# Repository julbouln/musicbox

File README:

Deprecated, see https://github.com/julbouln/musicboxV2

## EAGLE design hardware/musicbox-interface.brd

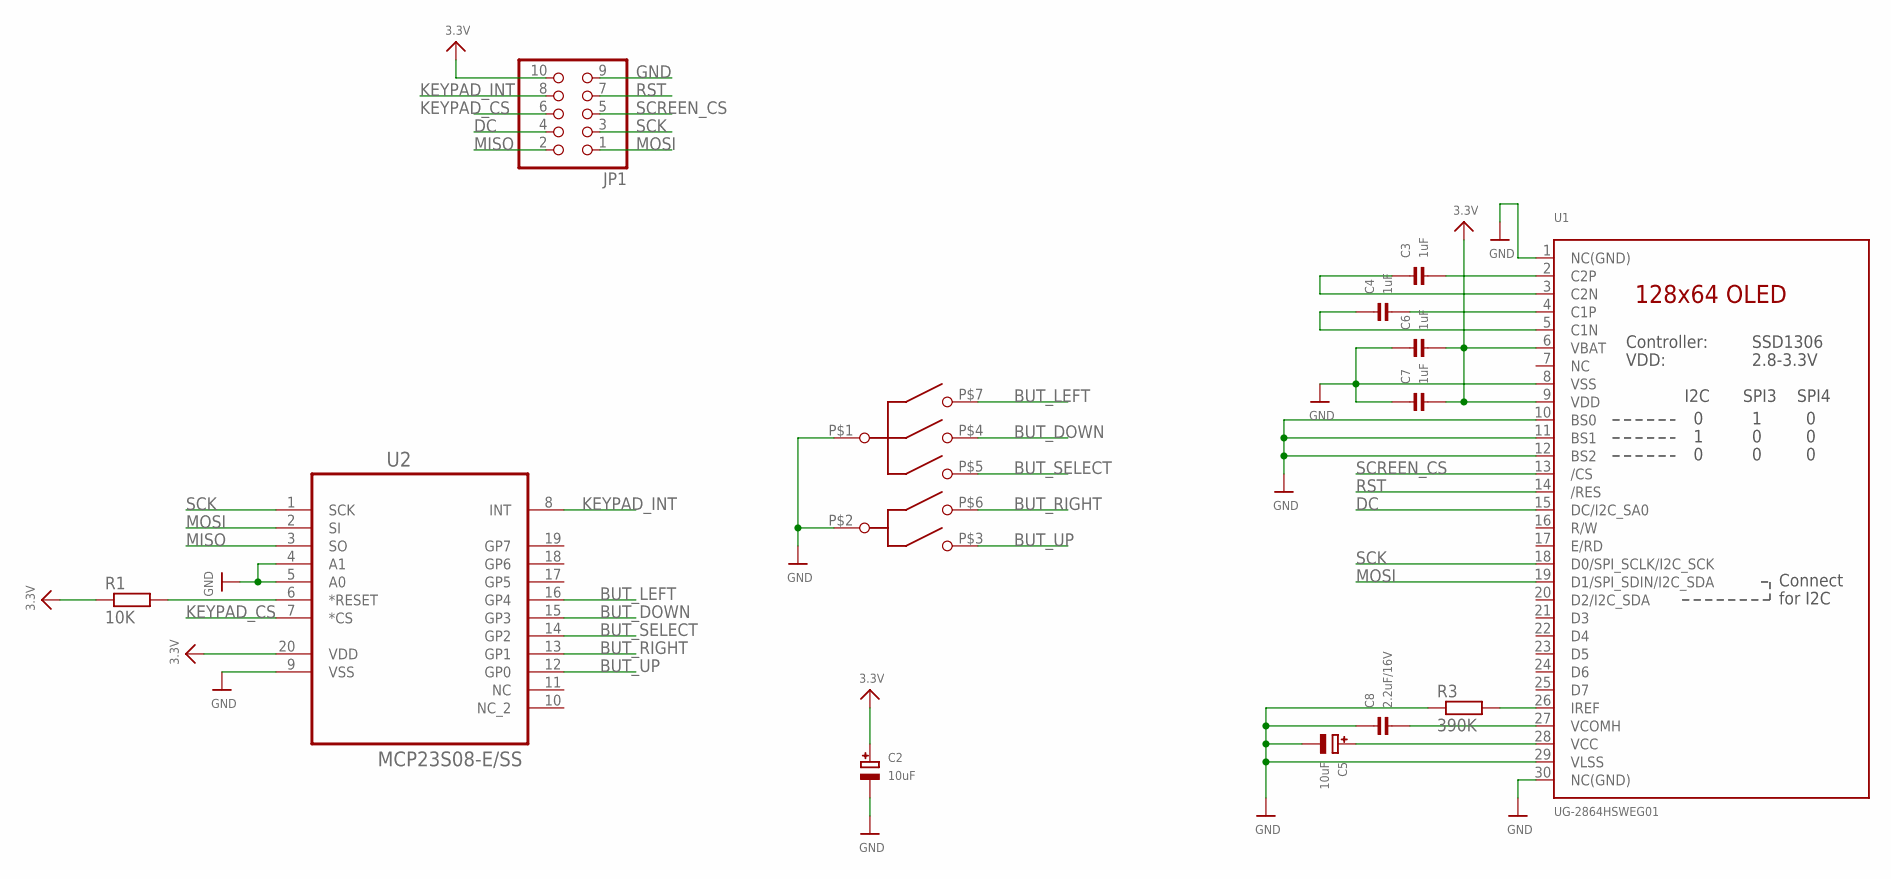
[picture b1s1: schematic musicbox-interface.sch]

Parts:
C2, C5: 10uF; EIA3216-18/A-R
C3, C4, C6, C7: 1uF; 0603
C8: 2.2uF/16V; 0603
JP1: HEADER-2X5; 2X05
R1: 10K; R0603
R3: 390K; R0603
U1: UG-2864HSWEG01; UG-2864HSWEG01_0.96IN_WRAPAROUND
U2: MCP23S08-E/SS; SOP65P780X200-20N
U$5: TPA; SMT

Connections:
3.3V: C2.+, C6.2, C7.2, JP1.10, R1.1, U1.6 (VBAT), U1.9 (VDD), U2.20 (VDD)
BUT_DOWN: U2.15 (GP3), U$5.P$4 (DOWN)
BUT_LEFT: U2.16 (GP4), U$5.P$7 (LEFT)
BUT_RIGHT: U2.13 (GP1), U$5.P$6 (RIGHT)
BUT_SELECT: U2.14 (GP2), U$5.P$5 (SELECT)
BUT_UP: U2.12 (GP0), U$5.P$3 (UP)
DC: JP1.4, U1.15 (DC/I2C_SA0)
GND: C2.-, C5.-, C6.1, C7.1, C8.1, JP1.9, R3.1, U1.1 (NC(GND)), U1.8 (VSS), U1.10 (BS0), U1.11 (BS1), U1.12 (BS2), U1.29 (VLSS), U1.30 (NC(GND)), U2.4 (A1), U2.5 (A0), U2.9 (VSS), U$5.P$1 (COMMON_1), U$5.P$2 (COMMON_2)
KEYPAD_CS: JP1.6, U2.7 (*CS)
KEYPAD_INT: JP1.8, U2.8 (INT)
MISO: JP1.2, U2.3 (SO)
MOSI: JP1.1, U1.19 (D1/SPI_SDIN/I2C_SDA), U2.2 (SI)
unnamed: C5.+, U1.28 (VCC)
unnamed: R1.2, U2.6 (*RESET)
unnamed: R3.2, U1.26 (IREF)
unnamed: C3.2, U1.2 (C2P)
unnamed: C3.1, U1.3 (C2N)
unnamed: C4.2, U1.4 (C1P)
unnamed: C4.1, U1.5 (C1N)
unnamed: C8.2, U1.27 (VCOMH)
RST: JP1.7, U1.14 (/RES)
SCK: JP1.3, U1.18 (D0/SPI_SCLK/I2C_SCK), U2.1 (SCK)
SCREEN_CS: JP1.5, U1.13 (/CS)

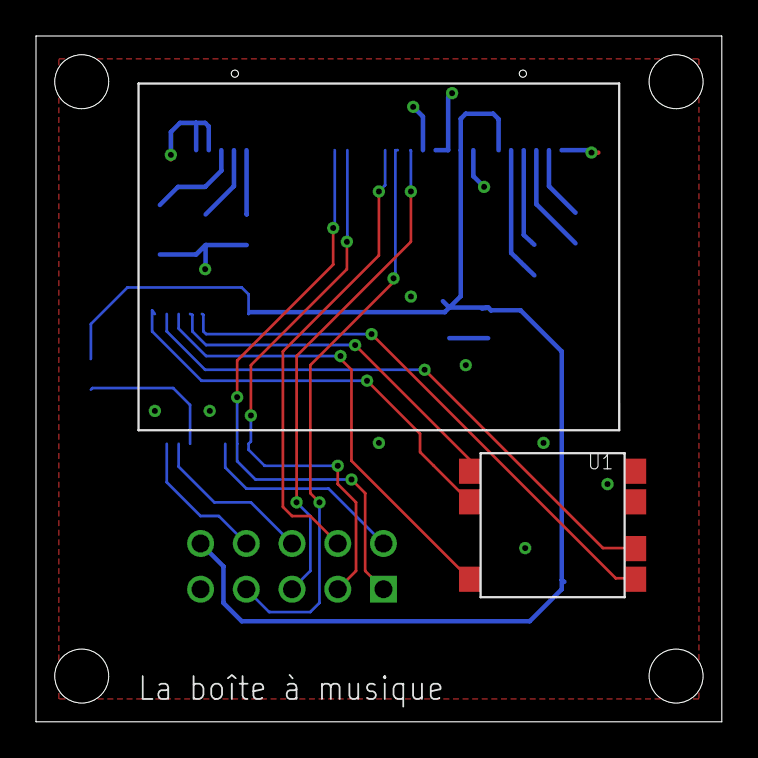
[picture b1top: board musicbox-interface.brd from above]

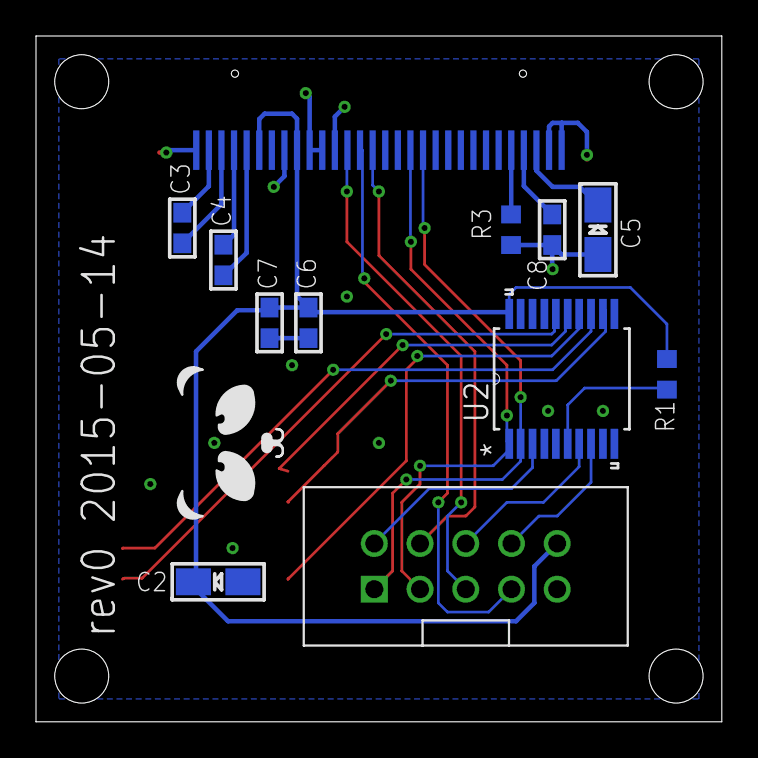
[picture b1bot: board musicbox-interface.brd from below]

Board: 2 copper layers, 38.1 x 38.1 mm, 14 parts (12 on the bottom side), 23 nets.

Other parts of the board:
U$8: PANDA

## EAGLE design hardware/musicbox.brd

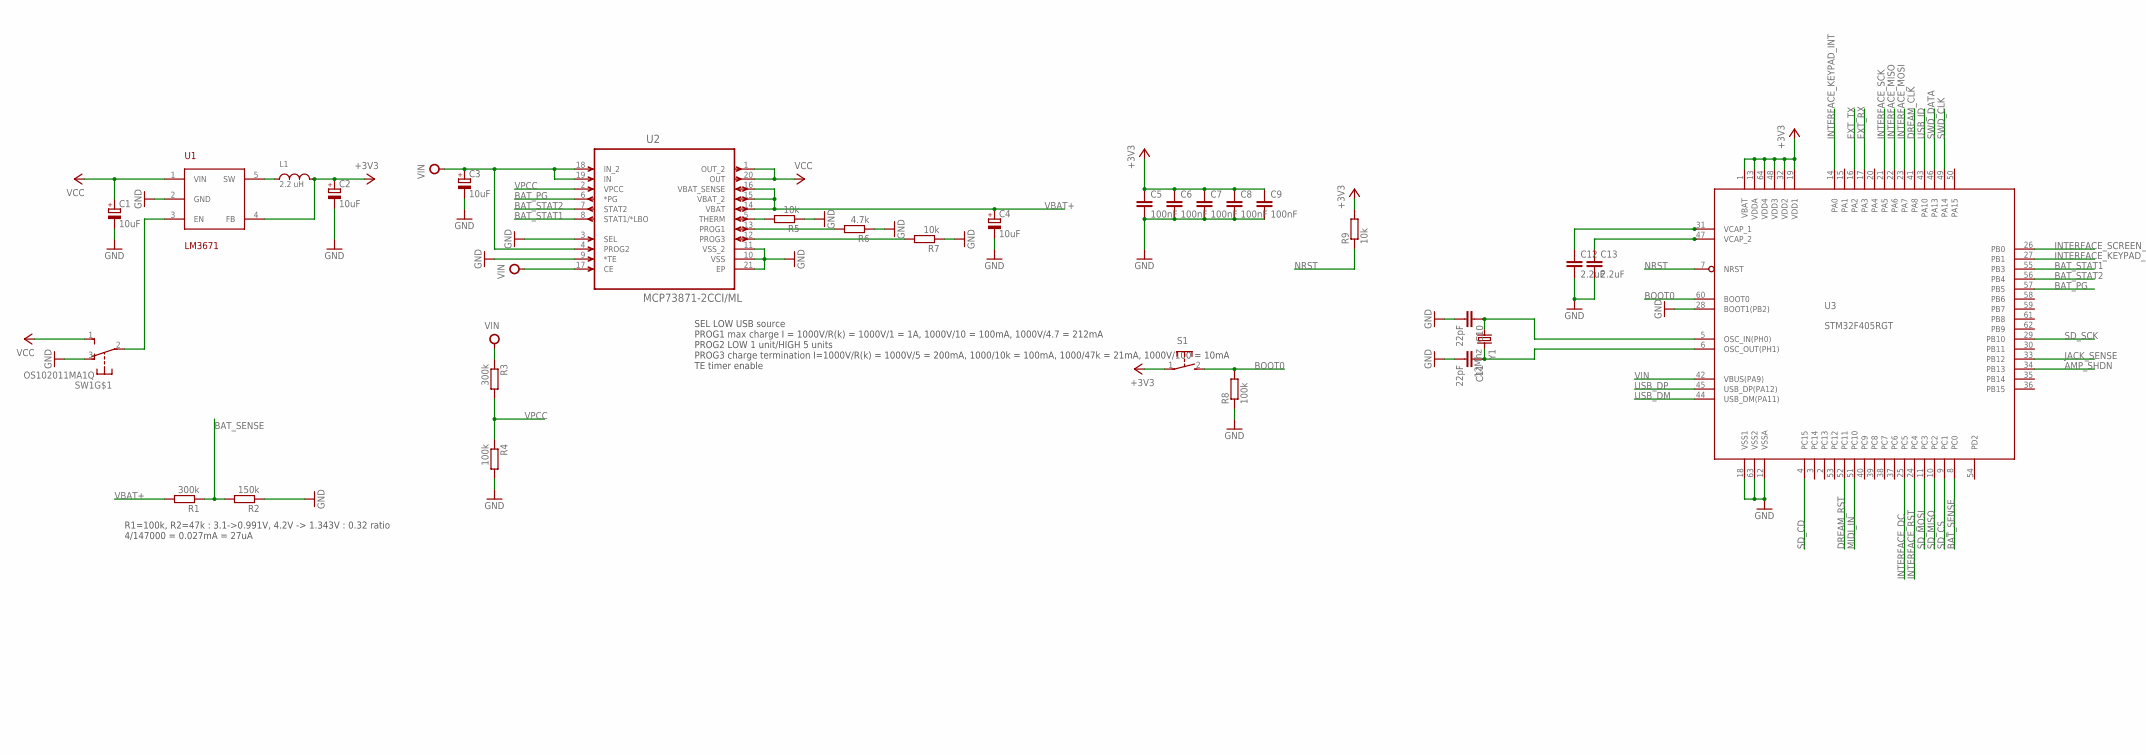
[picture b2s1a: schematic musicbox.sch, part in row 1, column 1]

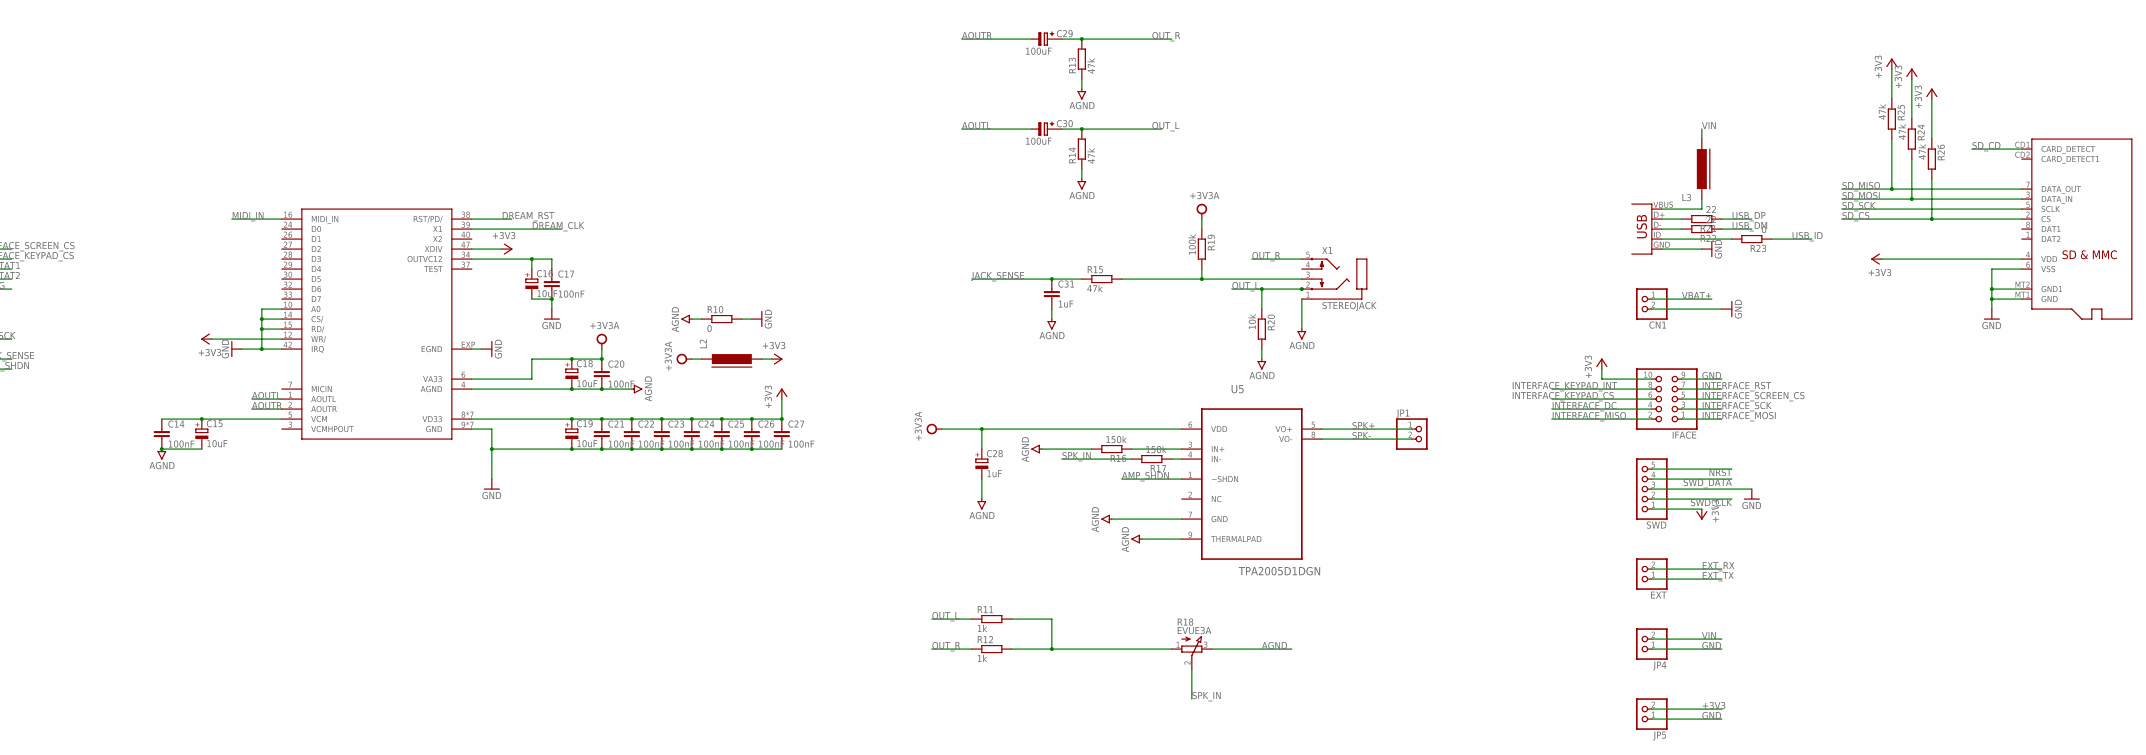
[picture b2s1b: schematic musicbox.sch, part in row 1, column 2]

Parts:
C1, C2, C3, C4, C15, C16, C18, C19: 10uF; A/3216-18R
C5, C6, C7, C8, C9, C14, C17, C20, C21, C22, C23, C24, C25, C26, C27: 100nF; C0603K
C10, C11: 22pF; C0603K
C12, C13: 2.2uF; C0603K
C28: 1uF; A/3216-18R
C29, C30: 100uF; SV-B
C31: 1uF; C0603K
CN1: JST_2PIN-THM; JST-PH-2-THM
EXT: HEADER-1X2ROUND; 1X02_ROUND
IFACE: HEADER-2X5; 2X05
JP1, JP4, JP5: HEADER-1X2ROUND; 1X02_ROUND
L1: 2.2 uH; 4X4MM
L2, L3: FERRITE-0603; FB603
R1, R3: 300k; R0603
R2, R16, R17: 150k; R0603
R4, R8, R19: 100k; R0603
R5, R7, R9, R20: 10k; R0603
R6: 4.7k; R0603
R10, R23: 0; R0603
R11, R12: 1k; R0603
R13, R14, R15, R24, R25, R26: 47k; R0603
R18: EVUE3A; EVUE
R21, R22: 22; R0603
S1: 31-XX; B3F-31XX
SW1: OS102011MA1Q
SWD: HEADER-1X5ROUND; 1X05_ROUND
U1: LM3671; SOT23-5
U2: MCP73871-2CCI/ML; QFN50P400X400X100-21N
U3: STM32F405RGT; LQFP64
U4: SAM2695; QFN48
U5: TPA2005D1DGN; SOP65P488X107-9N
U6: MICROSD
X1: STEREOJACK; STX3100
X2: USB-MICROB-SMD
Y1: 12Mhz; CRYSTAL-TXC-7A

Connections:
+3V3: C2.+, C5.1, C6.1, C7.1, C8.1, C9.1, C19.+, C21.1, C22.1, C23.1, C24.1, C25.1, C26.1, C27.1, IFACE.10, JP5.2, L1.2, L2.2, R9.2, R24.1, R25.1, R26.1, S1.1, SWD.1, U1.4 (FB), U3.1 (VBAT), U3.13 (VDDA), U3.19 (VDD1), U3.32 (VDD2), U3.48 (VDD3), U3.64 (VDD4), U4.8 (VD33), U4.11 (VD33), U4.12 (WR/), U4.20 (VD33), U4.31 (VD33), U4.35 (VD33), U4.41 (VD33), U4.46 (VD33), U4.47 (XDIV), U6.4 (VDD)
+3V3A: C18.+, C20.1, C28.+, L2.1, R19.1, U4.6 (VA33), U5.6 (VDD)
AGND: C14.2, C15.-, C18.-, C20.2, C28.-, C31.2, R10.1, R13.1, R14.1, R16.2, R18.3 (E), R20.2, U4.4 (AGND), U5.7 (GND), U5.9 (THERMALPAD), X1.1
AMP_SHDN: U3.34 (PB13), U5.1 (~SHDN)
AOUTL: C30.-, U4.1 (AOUTL)
AOUTR: C29.-, U4.2 (AOUTR)
BAT_PG: U2.6 (*PG), U3.57 (PB5)
BAT_SENSE: R1.1, R2.2, U3.8 (PC0)
BAT_STAT1: U2.8 (STAT1/*LBO), U3.55 (PB3)
BAT_STAT2: U2.7 (STAT2), U3.56 (PB4)
BOOT0: R8.2, S1.2 (S), U3.60 (BOOT0)
DREAM_CLK: U3.41 (PA8), U4.39 (X1)
DREAM_RST: U3.52 (PC11), U4.38 (RST/PD/)
EXT_RX: EXT.2, U3.17 (PA3)
EXT_TX: EXT.1, U3.16 (PA2)
GND: C1.-, C2.-, C3.-, C4.-, C5.2, C6.2, C7.2, C8.2, C9.2, C10.2, C11.2, C12.2, C13.2, C16.-, C17.2, C19.-, C21.2, C22.2, C23.2, C24.2, C25.2, C26.2, C27.2, CN1.2 (1), IFACE.9, JP4.1, JP5.1, R2.1, R4.2, R5.1, R6.1, R7.1, R8.1, R10.2, SW1.3 (O), SWD.3, U1.2 (GND), U2.3 (SEL), U2.9 (*TE), U2.10 (VSS), U2.11 (VSS_2), U2.21 (EP), U3.12 (VSSA), U3.18 (VSS1), U3.28 (BOOT1(PB2)), U3.63 (VSS2), U4.9 (GND), U4.10 (A0), U4.13 (GND), U4.14 (CS/), U4.15 (RD/), U4.18 (GND), U4.25 (GND), U4.36 (GND), U4.42 (IRQ), U4.45 (GND), U4.48 (GND), U4.EXP (EGND), U6.6 (VSS), U6.MT1 (GND), U6.MT2 (GND1), X2.GND
INTERFACE_DC: IFACE.4, U3.25 (PC5)
INTERFACE_KEYPAD_CS: IFACE.6, U3.27 (PB1)
INTERFACE_KEYPAD_INT: IFACE.8, U3.14 (PA0)
INTERFACE_MISO: IFACE.2, U3.22 (PA6)
INTERFACE_MOSI: IFACE.1, U3.23 (PA7)
INTERFACE_RST: IFACE.7, U3.24 (PC4)
INTERFACE_SCK: IFACE.3, U3.21 (PA5)
INTERFACE_SCREEN_CS: IFACE.5, U3.26 (PB0)
JACK_SENSE: C31.1, R15.1, U3.33 (PB12)
MIDI_IN: U3.51 (PC10), U4.16 (MIDI_IN)
unnamed: C12.1, U3.31 (VCAP_1)
unnamed: C11.1, U3.6 (OSC_OUT(PH1)), Y1.P$2 (2)
unnamed: C10.1, U3.5 (OSC_IN(PH0)), Y1.P$1 (1)
unnamed: C16.+, C17.1, U4.34 (OUTVC12)
unnamed: C14.1, C15.+, U4.5 (VCM)
unnamed: R21.2, X2.D+
unnamed: C13.1, U3.47 (VCAP_2)
unnamed: L1.1, U1.5 (SW)
unnamed: R22.2, X2.D-
unnamed: SW1.2, U1.3 (EN)
unnamed: R23.2, X2.ID
unnamed: R5.2, U2.5 (THERM)
unnamed: L3.1, X2.VBUS
unnamed: R7.2, U2.12 (PROG3)
unnamed: R6.2, U2.13 (PROG1)
unnamed: R11.2, R12.2, R18.1 (A)
unnamed: R17.1, U5.4 (IN-)
unnamed: R16.1, U5.3 (IN+)
unnamed: R15.2, R19.2, X1.3
NRST: R9.1, SWD.5, U3.7 (NRST)
OUT_L: C30.+, R11.1, R14.2, R20.1, X1.2
OUT_R: C29.+, R12.1, R13.2, X1.5
SD_CD: U3.4 (PC15), U6.CD1 (CARD_DETECT)
SD_CS: R26.2, U3.9 (PC1), U6.2 (CS)
SD_MISO: R25.2, U3.10 (PC2), U6.7 (DATA_OUT)
SD_MOSI: R24.2, U3.11 (PC3), U6.3 (DATA_IN)
SD_SCK: U3.29 (PB10), U6.5 (SCLK)
SPK+: JP1.1, U5.5 (VO+)
SPK-: JP1.2, U5.8 (VO-)
SPK_IN: R17.2, R18.2 (S)
SWD_CLK: SWD.2, U3.49 (PA14)
SWD_DATA: SWD.4, U3.46 (PA13)
USB_DM: R22.1, U3.44 (USB_DM(PA11))
USB_DP: R21.1, U3.45 (USB_DP(PA12))
USB_ID: R23.1, U3.43 (PA10)
VBAT+: C4.+, CN1.1 (2), R1.2, U2.14 (VBAT), U2.15 (VBAT_2), U2.16 (VBAT_SENSE)
VCC: C1.+, SW1.1 (S), U1.1 (VIN), U2.1 (OUT_2), U2.20 (OUT)
VIN: C3.+, JP4.2, L3.2, R3.1, U2.4 (PROG2), U2.17 (CE), U2.18 (IN_2), U2.19 (IN), U3.42 (VBUS(PA9))
VPCC: R3.2, R4.1, U2.2 (VPCC)

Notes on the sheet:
SEL LOW USB source PROG1 max charge I = 1000V/R(k) = 1000V/1 = 1A, 1000V/10 = 100mA, 1000V/4.7 = 212mA PROG2 LOW 1 unit/HIGH 5 units PROG3 charge termination I=1000V/R(k) = 1000V/5 = 200mA, 1000/10k = 100mA, 1000/47k = 21mA, 1000V/100 = 10mA TE timer enable
R1=100k, R2=47k : 3.1->0.991V, 4.2V -> 1.343V : 0.32 ratio 4/147000 = 0.027mA = 27uA

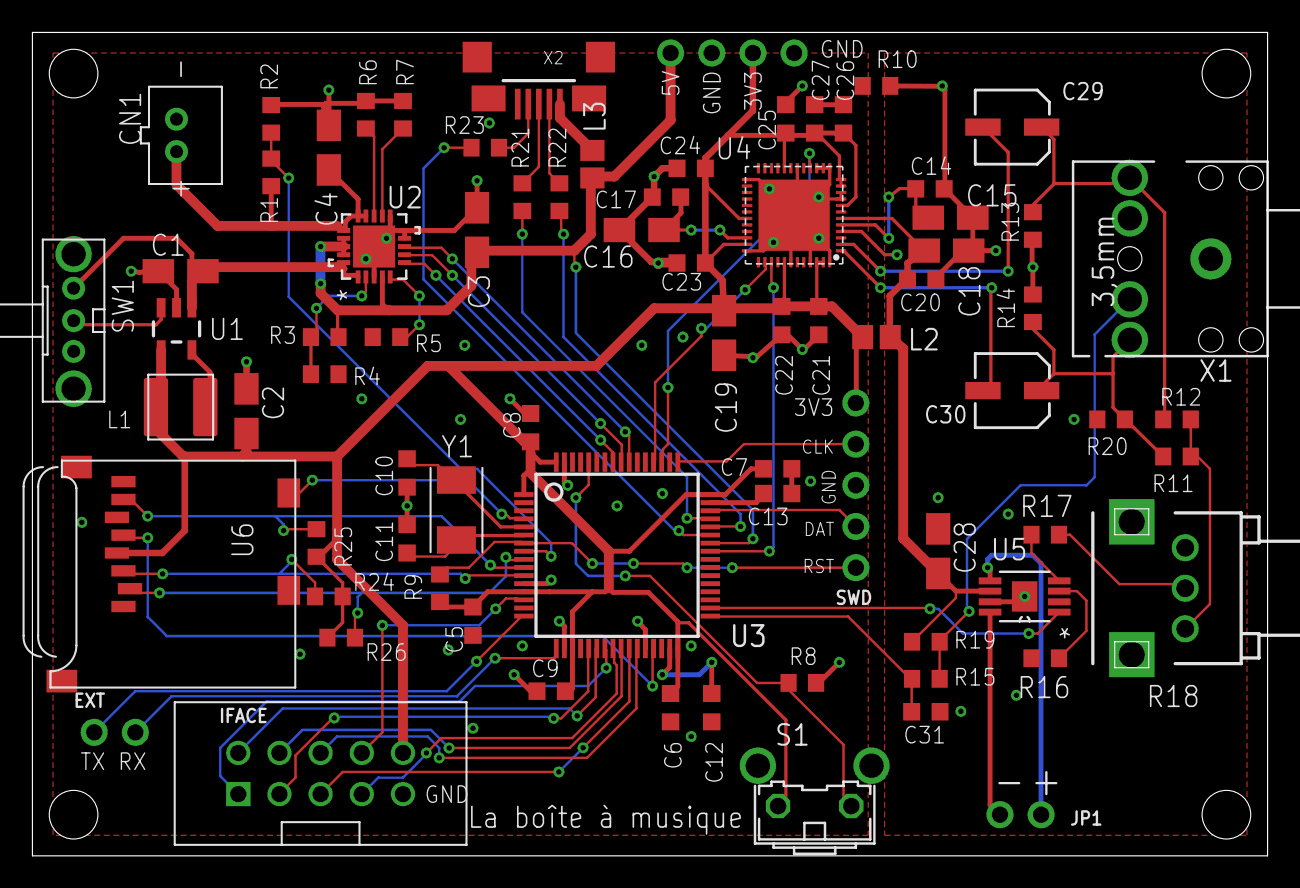
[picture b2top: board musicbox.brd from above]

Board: 2 copper layers, 76.2 x 50.8 mm, 79 parts (1 on the bottom side), 65 nets.

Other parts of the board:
U$1: PANDA

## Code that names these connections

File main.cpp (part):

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#define SCREEN_SCK	PA_5
#define SCREEN_DC	PC_5
#define SCREEN_RST	PC_4
#define SCREEN_CS	PB_0

#define PAD_MISO PA_6
#define PAD_CS PB_1
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#define MIDI_RST PC_11
#define MIDI_OUT PC_10

#define JACK_SENSE PB_12
#define AMP_SHDN PB_13

#define BAT_SENSE PC_0
#define BAT_STAT1 PB_3
#define BAT_STAT2 PB_4
#define BAT_PG PB_5

#define SD_CS PC_1
#define SD_MISO PC_2
#define SD_MOSI PC_3
#define SD_SCK PB_10
#define SD_CD PC_15

/* PAD */
#define PAD_TOP 0b10111
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
	HAL_RCC_MCOConfig(RCC_MCO1, RCC_MCO1SOURCE_HSE, RCC_MCODIV_1);   // select PLLCLK as source

	//Configure GPIO pin to output clock signal at  PA8
	//  (1 << (PA_8 & 0xF)) == GPIO_PIN_8
	InitStruct.Pin = GPIO_PIN_8;
	InitStruct.Mode = GPIO_MODE_AF_PP;
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
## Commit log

2015-06-20 cleanup
2015-06-20 add eagle schematics
2015-06-21 hardware
2016-02-20 deprecated

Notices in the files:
parts and their libraries:
SparkFun-FreqCtrl: Licensing: Creative Commons ShareAlike 4.0 International - https://creativecommons.org/licenses/by-sa/4.0
microbuilder: This work is placed in the public domain, and may be freely used for commercial and non-commercial work with the following conditions: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
